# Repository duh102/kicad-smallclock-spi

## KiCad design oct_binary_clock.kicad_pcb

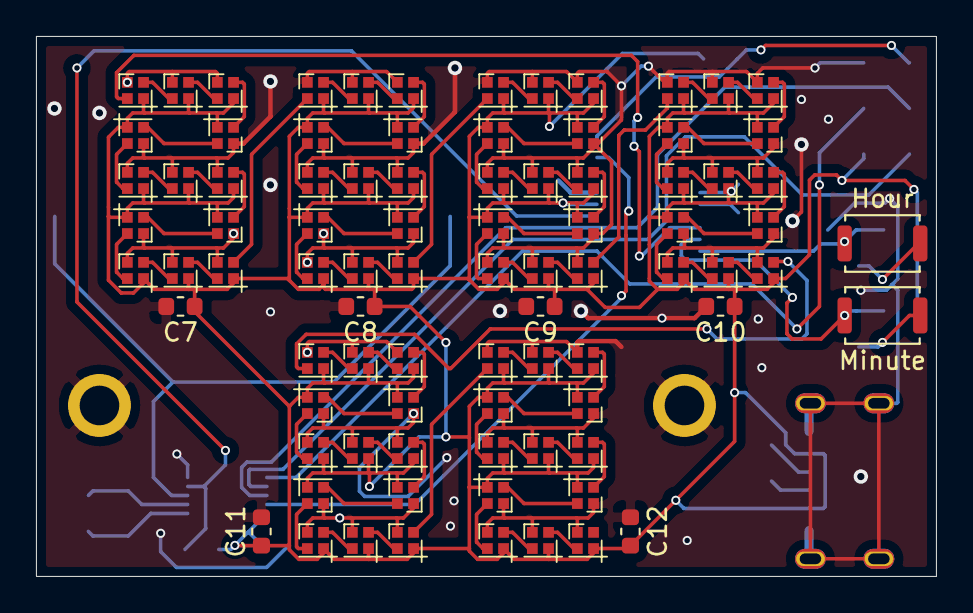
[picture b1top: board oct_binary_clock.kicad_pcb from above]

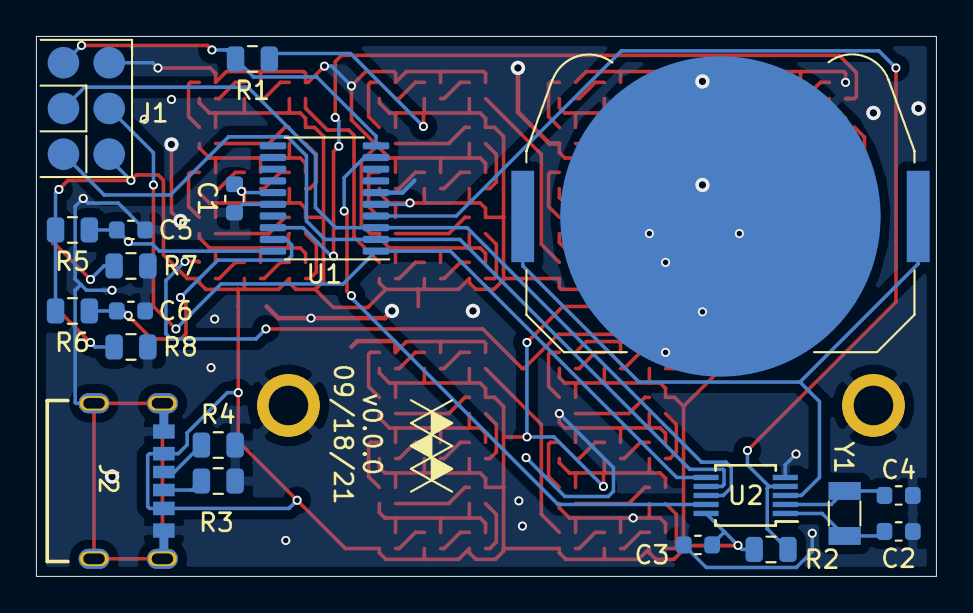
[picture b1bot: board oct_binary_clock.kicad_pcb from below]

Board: 2 copper layers, 50.0 x 30.0 mm, 106 parts (20 on the bottom side), 95 nets.

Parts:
BT1: 2032; BatteryHolder_Keystone_3034_1x20mm
C1, C3: 10kpF; C_0603_1608Metric
C2, C4: 16pF; C_0603_1608Metric
C5, C6: 1kpF; C_0603_1608Metric
C7, C8, C9, C10, C11, C12: C; C_0603_1608Metric
D1, D2, D3, D4, D5, D6, D7, D8, D9, D10, D11, D12, D13, D14, D15, D16, D17, D18, D19, D20, D21, D22, D23, D24, D25, D26, D27, D28, D29, D30, D31, D32, D33, D34, D35, D36, D37, D38, D39, D40, D41, D42, D43, D44, D45, D46, D47, D48, D49, D50, D51, D52, D53, D54, D55, D56, D57, D58, D59, D60, D61, D62, D63, D64, D65, D66, D67, D68, D69, D70, D71, D72, D73, D74, D75, D76, D77, D78: SK6805_1515-LED; LED_SK6805_PLCC4_1.5x1.5mm_P0.65mm
J1: AVR-ISP-6; pogo_pads_2x03_p2.54mm
J2: USB4125-GF-A_REVA2; GCT_USB4125-GF-A_REVA2
R1, R2, R5, R6: 10kR; R_0805_2012Metric
R3, R4: 5.11kR; R_0805_2012Metric
R7, R8: 1kR; R_0805_2012Metric
SW1, SW1#2: SW_Push; SW_Push_SPST_NO_Alps_SKRK
U1: ATtiny461A-XU; TSSOP-20_4.4x6.5mm_P0.65mm
U2: MCP79510; MSOP-10_3x3mm_P0.5mm
Y1: 9pF; Crystal_SMD_3215-2Pin_3.2x1.5mm

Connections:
/+5V: C1.1, C3.1, C7.1, C8.1, C9.1, C10.1, C11.1, C12.1, D1.4, D2.4, D3.4, D4.4, D5.4, D6.4, D7.4, D8.4, D9.4, D10.4, D11.4, D12.4, D13.4, D14.4, D15.4, D16.4, D17.4, D18.4, D19.4, D20.4, D21.4, D22.4, D23.4, D24.4, D25.4, D26.4, D27.4, D28.4, D29.4, D30.4, D31.4, D32.4, D33.4, D34.4, D35.4, D36.4, D37.4, D38.4, D39.4, D40.4, D41.4, D42.4, D43.4, D44.4, D45.4, D46.4, D47.4, D48.4, D49.4, D50.4, D51.4, D52.4, D53.4, D54.4, D55.4, D56.4, D57.4, D58.4, D59.4, D60.4, D61.4, D62.4, D63.4, D64.4, D65.4, D66.4, D67.4, D68.4, D69.4, D70.4, D71.4, D72.4, D73.4, D74.4, D75.4, D76.4, D77.4, D78.4, J1.2, J2.A9, J2.B9, R1.2, R2.2, R5.1, R6.1, U1.5, U1.15, U2.10
/DISP: D1.3, U1.18
/GND: BT1.2, C1.2, C2.2, C3.2, C4.2, C5.2, C6.2, C7.2, C8.2, C9.2, C10.2, C11.2, C12.2, D1.2, D2.2, D3.2, D4.2, D5.2, D6.2, D7.2, D8.2, D9.2, D10.2, D11.2, D12.2, D13.2, D14.2, D15.2, D16.2, D17.2, D18.2, D19.2, D20.2, D21.2, D22.2, D23.2, D24.2, D25.2, D26.2, D27.2, D28.2, D29.2, D30.2, D31.2, D32.2, D33.2, D34.2, D35.2, D36.2, D37.2, D38.2, D39.2, D40.2, D41.2, D42.2, D43.2, D44.2, D45.2, D46.2, D47.2, D48.2, D49.2, D50.2, D51.2, D52.2, D53.2, D54.2, D55.2, D56.2, D57.2, D58.2, D59.2, D60.2, D61.2, D62.2, D63.2, D64.2, D65.2, D66.2, D67.2, D68.2, D69.2, D70.2, D71.2, D72.2, D73.2, D74.2, D75.2, D76.2, D77.2, D78.2, J1.6, J2.A12, J2.B12, J2.Shield, R3.1, R4.2, R7.2, R8.2, U1.6, U1.16, U2.5
/HH: C5.1, R5.2, SW1#2.1, U1.20
/MFP: U1.9, U2.9
/MISO: J1.1, U1.2, U2.7
/MM: C6.1, R6.2, SW1.1, U1.19
/MOSI: J1.4, U1.1, U2.6
/RESET: J1.5, R1.1, U1.10
/SCK: J1.3, U1.3, U2.8
/h1/DIN: D13.1, D14.3
/m0/DIN: D26.1, D27.3
/m1/DIN: D39.1, D40.3
/s0/DIN: D52.1, D53.3
/s1/DIN: D65.1, D66.3
/~RTC_CS: R2.1, U1.4, U2.4
unnamed: BT1.1, U2.3
unnamed: C2.1, U2.1, Y1.1
unnamed: C4.1, U2.2, Y1.2
unnamed: D1.1, D2.3
unnamed: D2.1, D3.3
unnamed: D3.1, D4.3
unnamed: D4.1, D5.3
unnamed: D5.1, D6.3
unnamed: D6.1, D7.3
unnamed: D7.1, D8.3
unnamed: D8.1, D9.3
unnamed: D10.1, D11.3
unnamed: D9.1, D10.3
unnamed: D11.1, D12.3
unnamed: D12.1, D13.3
unnamed: D14.1, D15.3
unnamed: D15.1, D16.3
unnamed: D16.1, D17.3
unnamed: D17.1, D18.3
unnamed: D18.1, D19.3
unnamed: D19.1, D20.3
unnamed: D20.1, D21.3
unnamed: D21.1, D22.3
unnamed: D22.1, D23.3
unnamed: D23.1, D24.3
unnamed: D24.1, D25.3
unnamed: D25.1, D26.3
unnamed: D27.1, D28.3
unnamed: D28.1, D29.3
unnamed: D29.1, D30.3
unnamed: D30.1, D31.3
unnamed: D31.1, D32.3
unnamed: D32.1, D33.3
unnamed: D33.1, D34.3
unnamed: D34.1, D35.3
unnamed: D35.1, D36.3
unnamed: D36.1, D37.3
unnamed: D37.1, D38.3
unnamed: D38.1, D39.3
unnamed: D40.1, D41.3
unnamed: D41.1, D42.3
unnamed: D42.1, D43.3
unnamed: D43.1, D44.3
unnamed: D44.1, D45.3
unnamed: D45.1, D46.3
unnamed: D46.1, D47.3
unnamed: D47.1, D48.3
unnamed: D48.1, D49.3
unnamed: D49.1, D50.3
unnamed: D50.1, D51.3
unnamed: D51.1, D52.3
unnamed: D53.1, D54.3
unnamed: D54.1, D55.3
unnamed: D55.1, D56.3
unnamed: D56.1, D57.3
unnamed: D57.1, D58.3
unnamed: D58.1, D59.3
unnamed: D59.1, D60.3
unnamed: D60.1, D61.3
unnamed: D61.1, D62.3
unnamed: D62.1, D63.3
unnamed: D63.1, D64.3
unnamed: D64.1, D65.3
unnamed: D66.1, D67.3
unnamed: D67.1, D68.3
unnamed: D68.1, D69.3
unnamed: D69.1, D70.3
unnamed: D70.1, D71.3
unnamed: D71.1, D72.3
unnamed: D72.1, D73.3
unnamed: D73.1, D74.3
unnamed: D74.1, D75.3
unnamed: D75.1, D76.3
unnamed: D76.1, D77.3
unnamed: D77.1, D78.3
unnamed: J2.A5, R3.2
unnamed: J2.B5, R4.1
unnamed: R7.1, SW1#2.2
unnamed: R8.1, SW1.2
